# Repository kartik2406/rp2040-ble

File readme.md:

# RP2040 BLE

A PCB that uses RP2040 MCU and HM-BT4502 BLE passthrough module.
This enables the RP2040 to communicated with other devices using Bluetooth.
The bluetooth module is connected via UART(0)

## 3D

## PCB front layer

## PCB back layer

## Generating board images
I used the gerber viewer on [PCBWay](https://www.pcbway.com/project/OnlineGerberViewer.html),
Downloaded the SVG renders from it, then converted the top and bottom SVGs to PNGs

## Helpful tutorials
- [The RP2040 hardware design guide, its in depth and cover things nicely](https://datasheets.raspberrypi.com/rp2040/hardware-design-with-rp2040.pdf)
- [An Intro to KiCad – Part 1: How PCBs Are Made](https://www.youtube.com/watch?v=vaCVh2SAZY4&list=PLEBQazB0HUyR24ckSZ5u05TZHV9khgA1O&ab_channel=Digi-Key)
- [Hardware Design with the RP2040: Custom PCB Based on the Raspberry Pi Pico](https://www.youtube.com/watch?v=kcwvuwetgEQ&ab_channel=Digi-Key)
- [Raspberry Pi RP2040 Hardware Design](https://www.youtube.com/watch?v=X00Cm5LMNQk&ab_channel=Phil%E2%80%99sLab)
- [KiCad STM32 + USB + Buck Converter PCB Design](https://www.youtube.com/watch?v=C7-8nUU6e3E&ab_channel=Phil%E2%80%99sLab)
- [KiCad 6 STM32 PCB Design Full Tutorial ](https://www.youtube.com/watch?v=aVUqaB0IMh4&ab_channel=Phil%E2%80%99sLab)
- [Designing a PCB for the RP2040 Microcontroller](https://www.teachmemicro.com/designing-a-pcb-for-the-rp2040-microcontroller/)
## Credits
- Most of the tutorial videos are from [Shawn Hymel](https://www.youtube.com/c/ShawnHymel), [Phil’s Lab](https://www.youtube.com/c/PhilS94).
They have amazing content do check them out.
- [Reddit PCB review thread](https://www.reddit.com/r/PrintedCircuitBoard/comments/wz8so7/pcb_review_rp2040_based_ble_board/),
thank you [Worldly-Protection-8](https://www.reddit.com/user/Worldly-Protection-8/), [DNosnibor](https://www.reddit.com/user/DNosnibor/) for the valuable review and feedback.

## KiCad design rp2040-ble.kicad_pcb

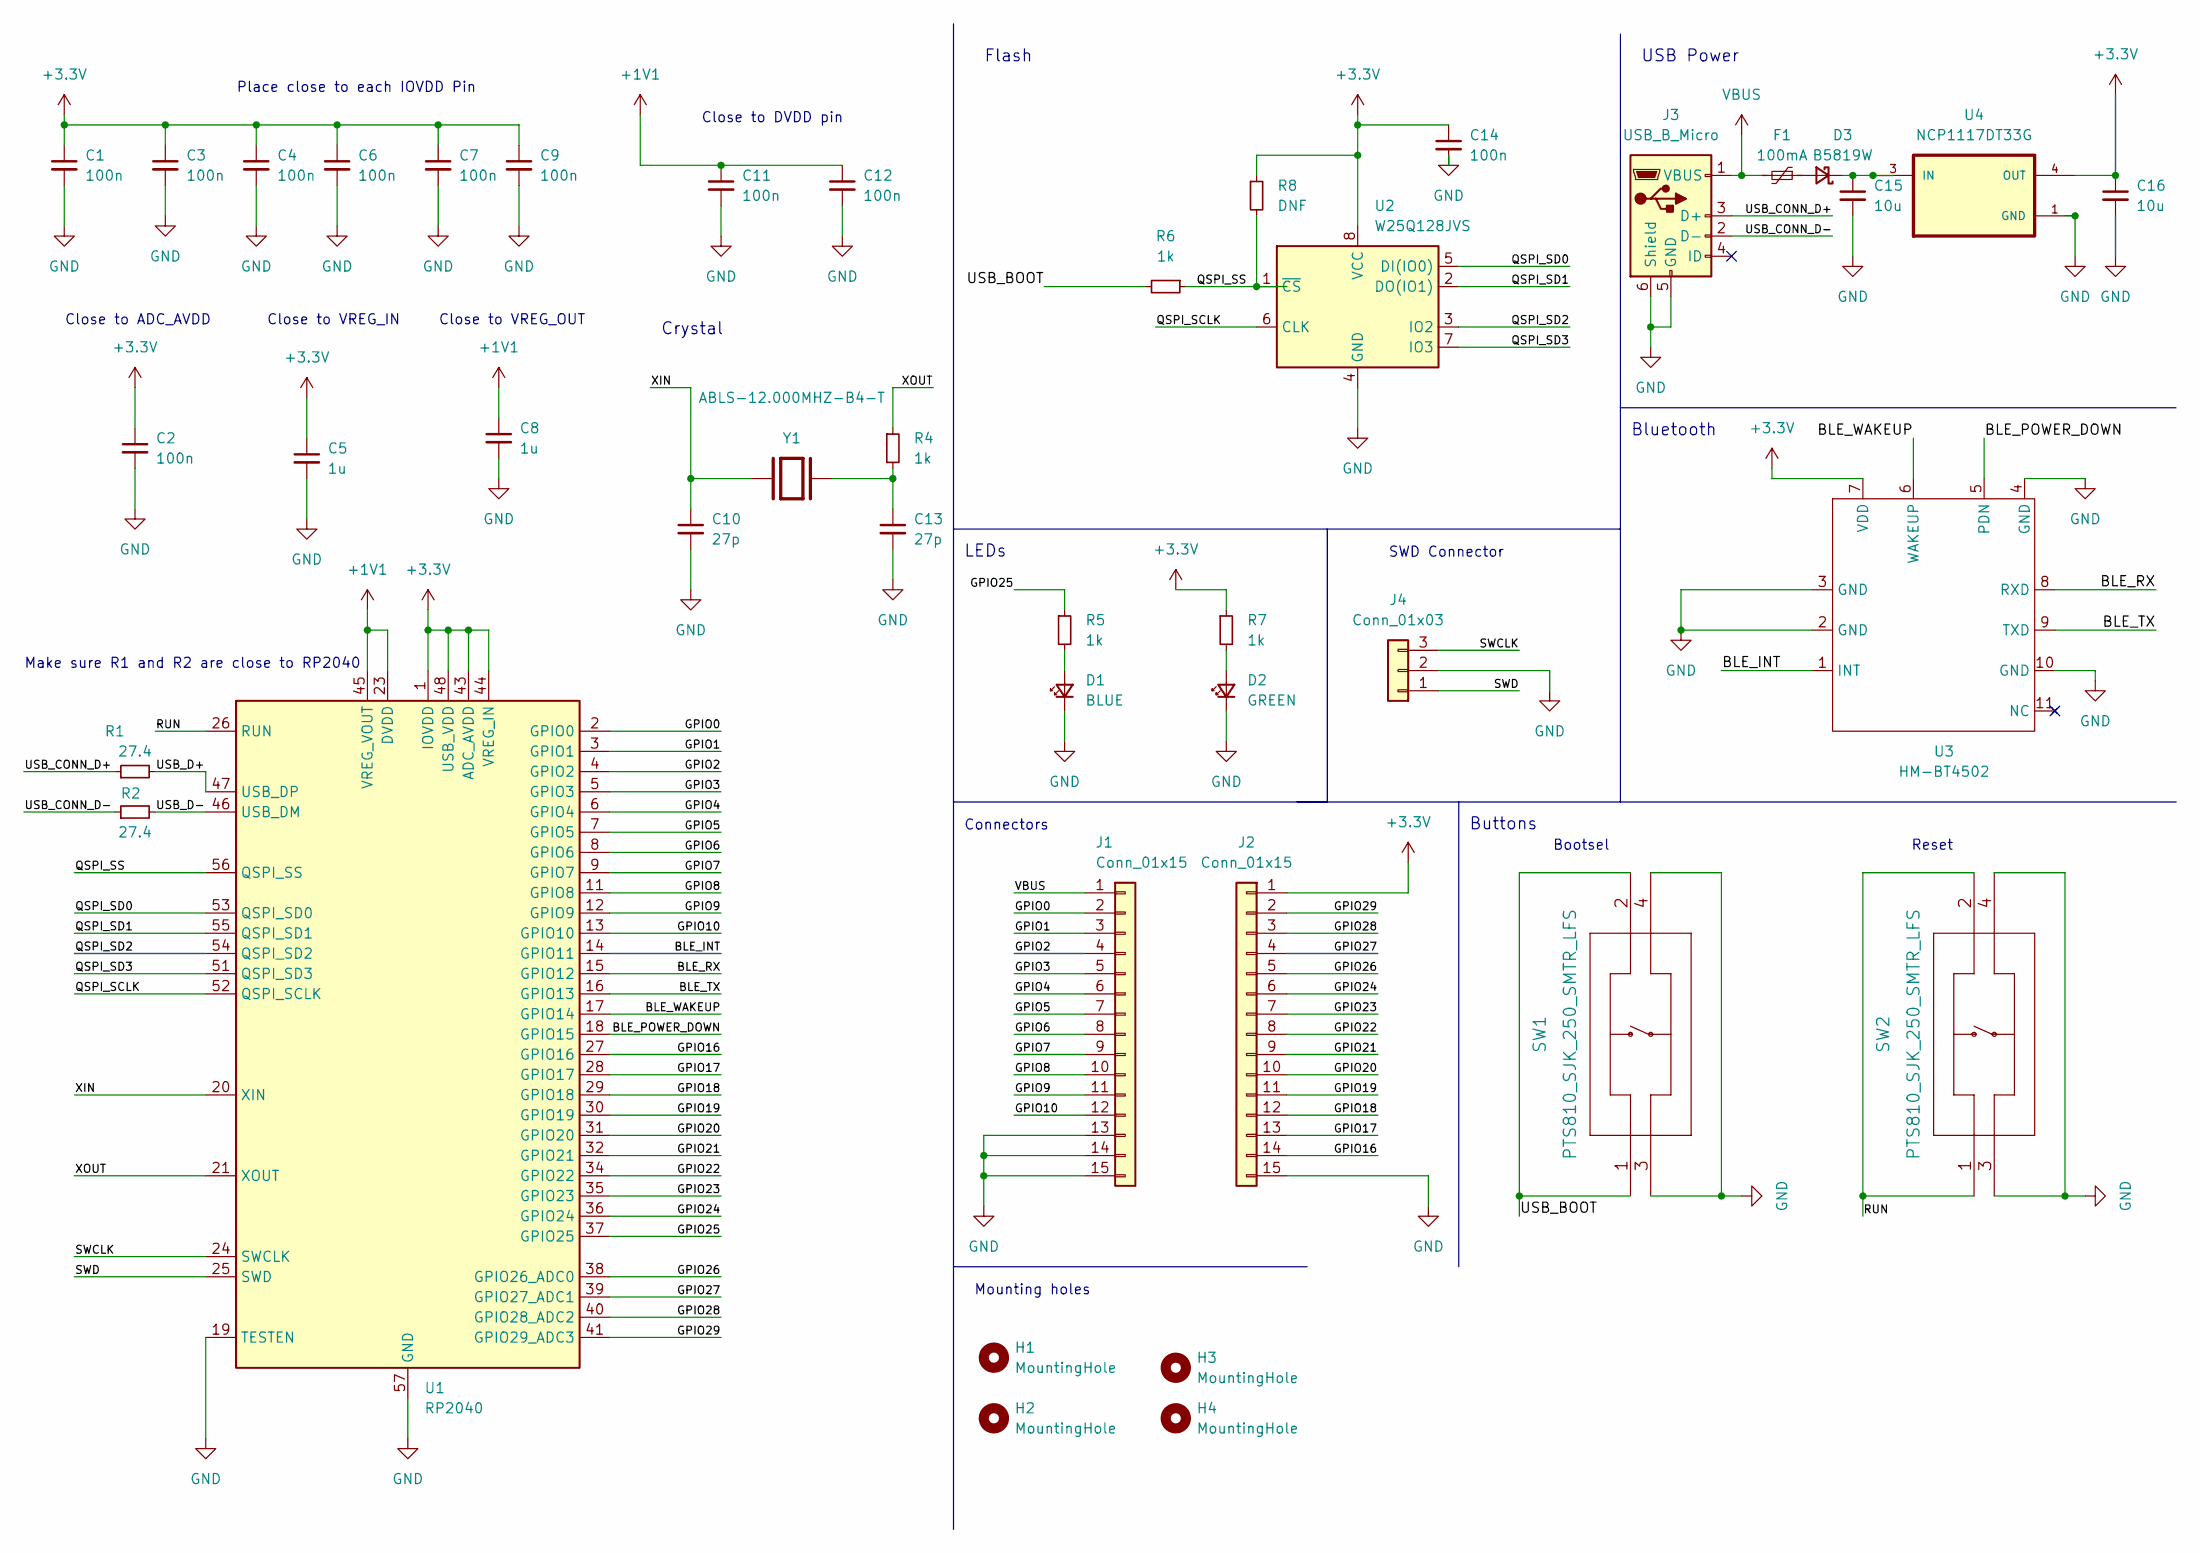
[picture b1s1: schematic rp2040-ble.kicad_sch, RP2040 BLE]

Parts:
C1, C2, C3, C4, C6, C7, C9, C11, C12, C14: 100n; C_0402_1005Metric
C5, C8: 1u; C_0402_1005Metric
C10, C13: 27p; C_0402_1005Metric
C15, C16: 10u; C_0603_1608Metric
D1: BLUE; LED_0603_1608Metric
D2: GREEN; LED_0603_1608Metric
D3: B5819W; D_SOD-123
F1: 100mA; Fuse_0603_1608Metric
H1, H2, H3, H4: MountingHole; MountingHole_2.2mm_M2
J1, J2: Conn_01x15; PinSocket_1x15_P2.54mm_Vertical
J3: USB_B_Micro; USB_Micro-B_Amphenol_10103594-0001LF_Horizontal
J4: Conn_01x03; PinHeader_1x03_P1.27mm_Vertical
R1, R2: 27.4; R_0402_1005Metric
R4, R5, R6, R7: 1k; R_0402_1005Metric
R8: DNF; R_0402_1005Metric
SW1, SW2: PTS810_SJK_250_SMTR_LFS; PTS810 SJK 250 SMTR LFS
U1: RP2040; QFN-56-1EP_7x7mm_P0.4mm_EP3.2x3.2mm
U2: W25Q128JVS; SOIC-8_5.23x5.23mm_P1.27mm
U3: HM-BT4502; MODULE_HM-BT4502
U4: NCP1117DT33G; VREG_NCP1117DT33G
Y1: ABLS-12.000MHZ-B4-T; XTAL_ABLS-12.000MHZ-B4-T; PARTREV 02.16.2021

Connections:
+1V1: C8.1, C11.1, C12.1, U1.23 (DVDD), U1.45 (VREG_VOUT), U1.50 (DVDD)
+3.3V: C1.1, C2.1, C3.1, C4.1, C5.1, C6.1, C7.1, C9.1, C14.1, C16.1, J2.1, R7.1, R8.1, U1.1 (IOVDD), U1.10 (IOVDD), U1.22 (IOVDD), U1.33 (IOVDD), U1.42 (IOVDD), U1.43 (ADC_AVDD), U1.44 (VREG_IN), U1.48 (USB_VDD), U1.49 (IOVDD), U2.8 (VCC), U3.7 (VDD), U4.4 (OUT)
/BLE_INT: U1.14 (GPIO11), U3.1 (INT)
/BLE_POWER_DOWN: U1.18 (GPIO15), U3.5 (PDN)
/BLE_RX: U1.15 (GPIO12), U3.8 (RXD)
/BLE_TX: U1.16 (GPIO13), U3.9 (TXD)
/BLE_WAKEUP: U1.17 (GPIO14), U3.6 (WAKEUP)
/GPIO0: J1.2, U1.2 (GPIO0)
/GPIO1: J1.3, U1.3 (GPIO1)
/GPIO2: J1.4, U1.4 (GPIO2)
/GPIO3: J1.5, U1.5 (GPIO3)
/GPIO4: J1.6, U1.6 (GPIO4)
/GPIO5: J1.7, U1.7 (GPIO5)
/GPIO6: J1.8, U1.8 (GPIO6)
/GPIO7: J1.9, U1.9 (GPIO7)
/GPIO8: J1.10, U1.11 (GPIO8)
/GPIO9: J1.11, U1.12 (GPIO9)
/GPIO10: J1.12, U1.13 (GPIO10)
/GPIO16: J2.14, U1.27 (GPIO16)
/GPIO17: J2.13, U1.28 (GPIO17)
/GPIO18: J2.12, U1.29 (GPIO18)
/GPIO19: J2.11, U1.30 (GPIO19)
/GPIO20: J2.10, U1.31 (GPIO20)
/GPIO21: J2.9, U1.32 (GPIO21)
/GPIO22: J2.8, U1.34 (GPIO22)
/GPIO23: J2.7, U1.35 (GPIO23)
/GPIO24: J2.6, U1.36 (GPIO24)
/GPIO25: R5.1, U1.37 (GPIO25)
/GPIO26: J2.5, U1.38 (GPIO26_ADC0)
/GPIO27: J2.4, U1.39 (GPIO27_ADC1)
/GPIO28: J2.3, U1.40 (GPIO28_ADC2)
/GPIO29: J2.2, U1.41 (GPIO29_ADC3)
/QSPI_SCLK: U1.52 (QSPI_SCLK), U2.6 (CLK)
/QSPI_SD0: U1.53 (QSPI_SD0), U2.5 (DI(IO0))
/QSPI_SD1: U1.55 (QSPI_SD1), U2.2 (DO(IO1))
/QSPI_SD2: U1.54 (QSPI_SD2), U2.3 (IO2)
/QSPI_SD3: U1.51 (QSPI_SD3), U2.7 (IO3)
/QSPI_SS: R6.1, R8.2, U1.56 (QSPI_SS), U2.1 (~CS)
/RUN: SW2.1, SW2.2, U1.26 (RUN)
/SWCLK: J4.3, U1.24 (SWCLK)
/SWD: J4.1, U1.25 (SWD)
/USB_BOOT: R6.2, SW1.1, SW1.2
/USB_CONN_D+: J3.3 (D+), R1.1
/USB_CONN_D-: J3.2 (D-), R2.1
/USB_D+: R1.2, U1.47 (USB_DP)
/USB_D-: R2.2, U1.46 (USB_DM)
/XIN: C10.1, U1.20 (XIN), Y1.1
/XOUT: R4.1, U1.21 (XOUT)
GND: C1.2, C2.2, C3.2, C4.2, C5.2, C6.2, C7.2, C8.2, C9.2, C10.2, C11.2, C12.2, C13.2, C14.2, C15.2, C16.2, D1.1 (K), D2.1 (K), J1.13, J1.14, J1.15, J2.15, J3.5 (GND), J3.6 (Shield), J4.2, SW1.3, SW1.4, SW2.3, SW2.4, U1.19 (TESTEN), U1.57 (GND), U2.4 (GND), U3.2 (GND), U3.3 (GND), U3.4 (GND), U3.10 (GND), U4.1 (GND)
unnamed: C13.1, R4.2, Y1.2
unnamed: C15.1, D3.1 (K), U4.3 (IN)
unnamed: D1.2 (A), R5.2
unnamed: D2.2 (A), R7.2
unnamed: D3.2 (A), F1.1
VBUS: F1.2, J1.1, J3.1 (VBUS)

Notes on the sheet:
LEDs
Buttons
Close to VREG_OUT
SWD Connector
Bootsel
Close to ADC_AVDD
Close to DVDD pin
Crystal
Bluetooth
Reset
Mounting holes
Flash
Close to VREG_IN
Make sure R1 and R2 are close to RP2040
Place close to each IOVDD Pin
USB Power
Connectors

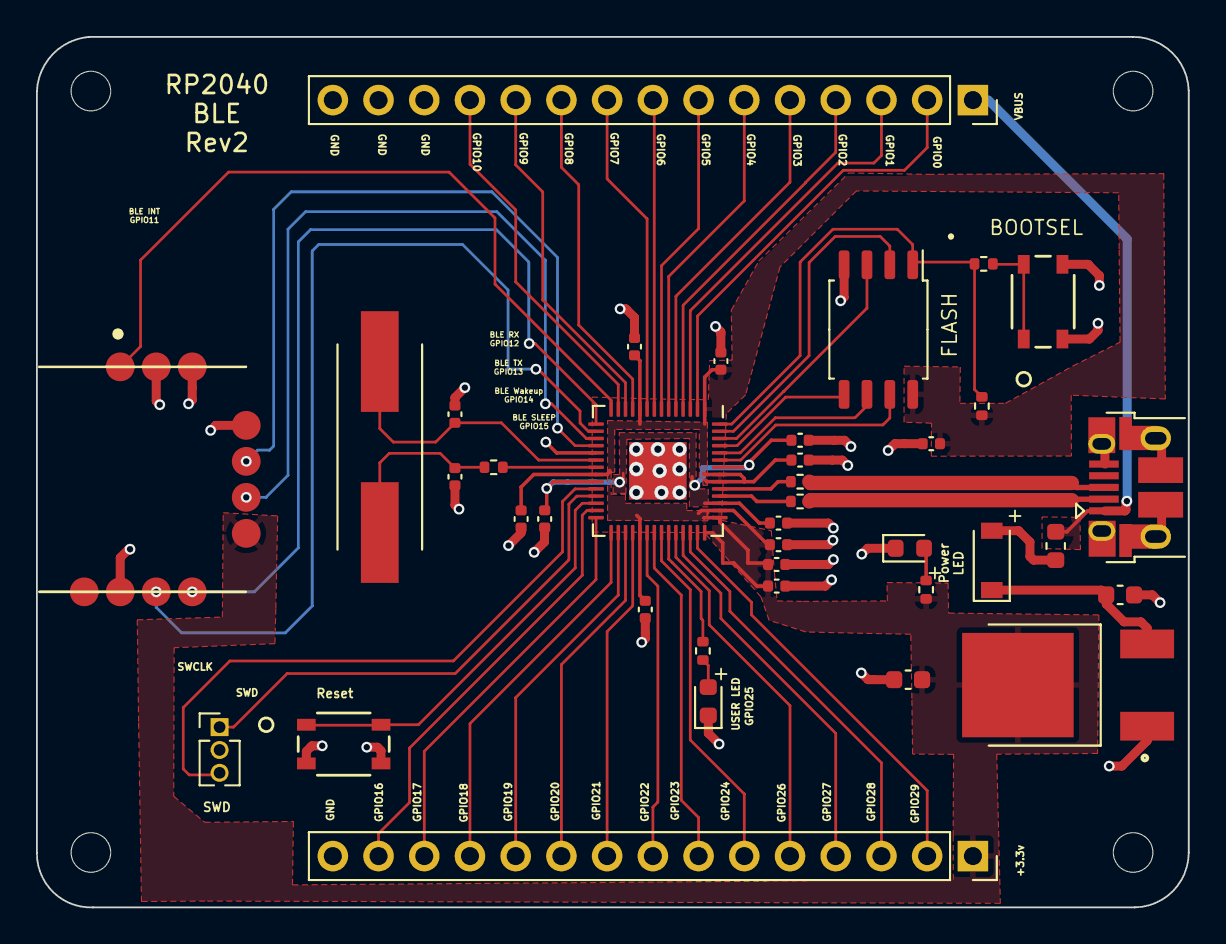
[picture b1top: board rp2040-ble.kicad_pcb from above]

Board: 2 copper layers, 64.0 x 48.4 mm, 42 parts (0 on the bottom side), 55 nets.

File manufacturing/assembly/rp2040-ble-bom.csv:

Source:,D:\electronic-schematics\rp2040-ble\rp2040-ble.kicad_sch,,,,,,
,,,,,,,
Date:,04-09-2022 9.00.25 PM,,,,,,
,,,,,,,
Tool:,Eeschema (6.0.6),,,,,,
,,,,,,,
Generator:,C:\Program Files\KiCad\6.0\bin\scripting\plugins/bom_csv_grouped_by_value_with_fp.py,,,,,,
,,,,,,,
Component Count:,42,,,,,,
,,,,,,,
Ref,Qnty,Value,Cmp name,Footprint,Description,Vendor,Robu ID
,,,,,,,
"C1, C2, C3, C4, C6, C7, C9, C11, C12, C14, ",10,100n,C_Small,Capacitor_SMD:C_0402_1005Metric,"Unpolarized capacitor, small symbol",CL05B104KO5NNNC,
,,,,,,,
"C5, C8, ",2,1u,C_Small,Capacitor_SMD:C_0402_1005Metric,"Unpolarized capacitor, small symbol",CL05A105KA5NQNC,
,,,,,,,
"C10, C13, ",2,27p,C_Small,Capacitor_SMD:C_0402_1005Metric,"Unpolarized capacitor, small symbol",CL05C270JB5NNNC,
,,,,,,,
"C15, C16, ",2,10u,C_Small,Capacitor_SMD:C_0603_1608Metric,"Unpolarized capacitor, small symbol",CL10A106KP8NNNC,
,,,,,,,
"D1, ",1,BLUE,LED_Small,LED_SMD:LED_0603_1608Metric,"Light emitting diode, small symbol",150060BS75000,
,,,,,,,
"D2, ",1,GREEN,LED_Small,LED_SMD:LED_0603_1608Metric,"Light emitting diode, small symbol",150060VS75000,
,,,,,,,
"D3, ",1,B5819W,D_Schottky_Small,Diode_SMD:D_SOD-123,"Schottky diode, small symbol",B5819W,
,,,,,,,
"F1, ",1,100mA,Polyfuse_Small,Fuse:Fuse_0603_1608Metric,"Resettable fuse, polymeric positive temperature coefficient, small symbol",0603L004YR,
,,,,,,,
"J1, J2, ",2,Conn_01x15,Conn_01x15,Connector_PinSocket_2.54mm:PinSocket_1x15_P2.54mm_Vertical,"Generic connector, single row, 01x15, script generated (kicad-library-utils/schlib/autogen/connector/)",,
,,,,,,,
"J3, ",1,USB_B_Micro,USB_B_Micro,Connector_USB:USB_Micro-B_Amphenol_10103594-0001LF_Horizontal,USB Micro Type B connector,10103594-0001LF,
,,,,,,,
"J4, ",1,Conn_01x03,Conn_01x03,Connector_PinHeader_1.27mm:PinHeader_1x03_P1.27mm_Vertical,"Generic connector, single row, 01x03, script generated (kicad-library-utils/schlib/autogen/connector/)",,
,,,,,,,
"R1, R2, ",2,27.4,R_Small,Resistor_SMD:R_0402_1005Metric,"Resistor, small symbol",RMCF0402FT27R4,
,,,,,,,
"R4, R5, R6, R7, ",4,1k,R_Small,Resistor_SMD:R_0402_1005Metric,"Resistor, small symbol",RC0402FR-071KL,
,,,,,,,
"R8, ",1,DNF,R_Small,Resistor_SMD:R_0402_1005Metric,"Resistor, small symbol",,
,,,,,,,
"SW1, SW2, ",2,PTS810_SJK_250_SMTR_LFS,PTS810_SJK_250_SMTR_LFS,PTS810:PTS810 SJK 250 SMTR LFS,,PTS810 SJK 250 SMTR LFS,
,,,,,,,
"U1, ",1,RP2040,RP2040,Package_DFN_QFN:QFN-56-1EP_7x7mm_P0.4mm_EP3.2x3.2mm,A microcontroller by Raspberry Pi,SC0914(7),997534
,,,,,,,
"U2, ",1,W25Q128JVS,W25Q128JVS,Package_SO:SOIC-8_5.23x5.23mm_P1.27mm,"128Mb Serial Flash Memory, Standard/Dual/Quad SPI, SOIC-8",W25Q128JVSIQ,
,,,,,,,
"U3, ",1,HM-BT4502,HM-BT4502,Custom:MODULE_HM-BT4502,,113990814,1195286
,,,,,,,
"U4, ",1,NCP1117DT33G,NCP1117DT33G,NCP1117DT33G:VREG_NCP1117DT33G,,NCP1117DT33G,
,,,,,,,
"Y1, ",1,ABLS-12.000MHZ-B4-T,ABLS-12.000MHZ-B4-T,ABLS-12:XTAL_ABLS-12.000MHZ-B4-T,,ABLS-12.000MHZ-B4-T,

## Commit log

2022-08-23 WIP Routing
2022-08-24 PCB roouting
2022-08-25 Updated routing, addedd 3d models for parts
2022-08-27 Add gerbers, fix pcb issues
2022-08-27 Add Images for review
2022-08-27 Update readme with images
2022-09-05 Incorporate review feedback
2022-09-06 Generate board screenshots
2022-09-06 Update the readme
2022-09-08 Add rev and missing liscense

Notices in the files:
rp2040-ble.kicad_pcb:
https://creativecommons.org/licenses/by/4.0
License: CC BY 4.0
parts and their libraries:
Copyright 2016 Accelerated Designs. All rights reserved.
